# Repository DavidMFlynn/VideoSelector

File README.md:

# VideoSelector
Sets camera to monitor connections, RS-232, Extron Electronics MAV 88, PIC16F1847.
Created by David M. Flynn 2017
I could find one, so I built one.
The main pcb and selector switch pcbs are connected by ethernet patch cables.
Each station can select (with a gray code rotory encoder) which cammera to view.
Box 3D has a 3D printable box.

The PCBs are made with kicad.  Two of the wires on port 2 are swapped, fixed in software.
I know its unlikely anyone will want one, but it makes a good example project.

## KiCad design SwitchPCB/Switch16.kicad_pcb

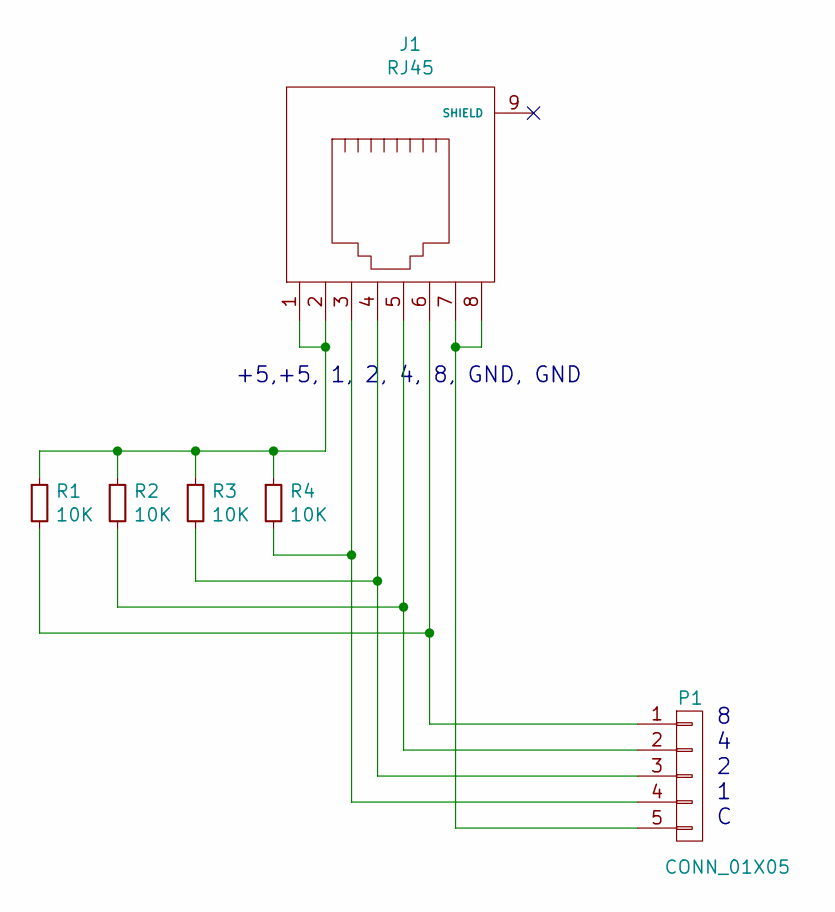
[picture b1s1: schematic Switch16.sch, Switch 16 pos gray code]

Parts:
J1: RJ45; RJ45_8
P1: CONN_01X05; Pin_Header_Straight_1x05
R1, R2, R3, R4: 10K; R_0805_HandSoldering

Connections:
unnamed: J1.1, J1.2, R1.1, R2.1, R3.1, R4.1
unnamed: J1.3, P1.4, R4.2
unnamed: J1.4, P1.3, R3.2
unnamed: J1.5, P1.2, R2.2
unnamed: J1.6, P1.1, R1.2
unnamed: J1.7, J1.8, P1.5

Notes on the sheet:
8 4 2 1 C
+5,+5, 1, 2, 4, 8, GND, GND

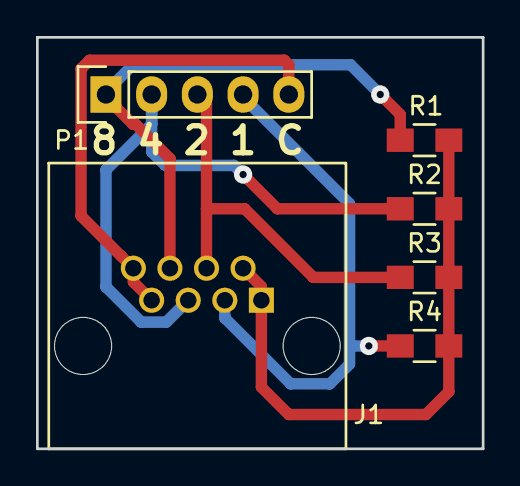
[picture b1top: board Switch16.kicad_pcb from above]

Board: 2 copper layers, 24.8 x 22.9 mm, 6 parts (0 on the bottom side), 6 nets.

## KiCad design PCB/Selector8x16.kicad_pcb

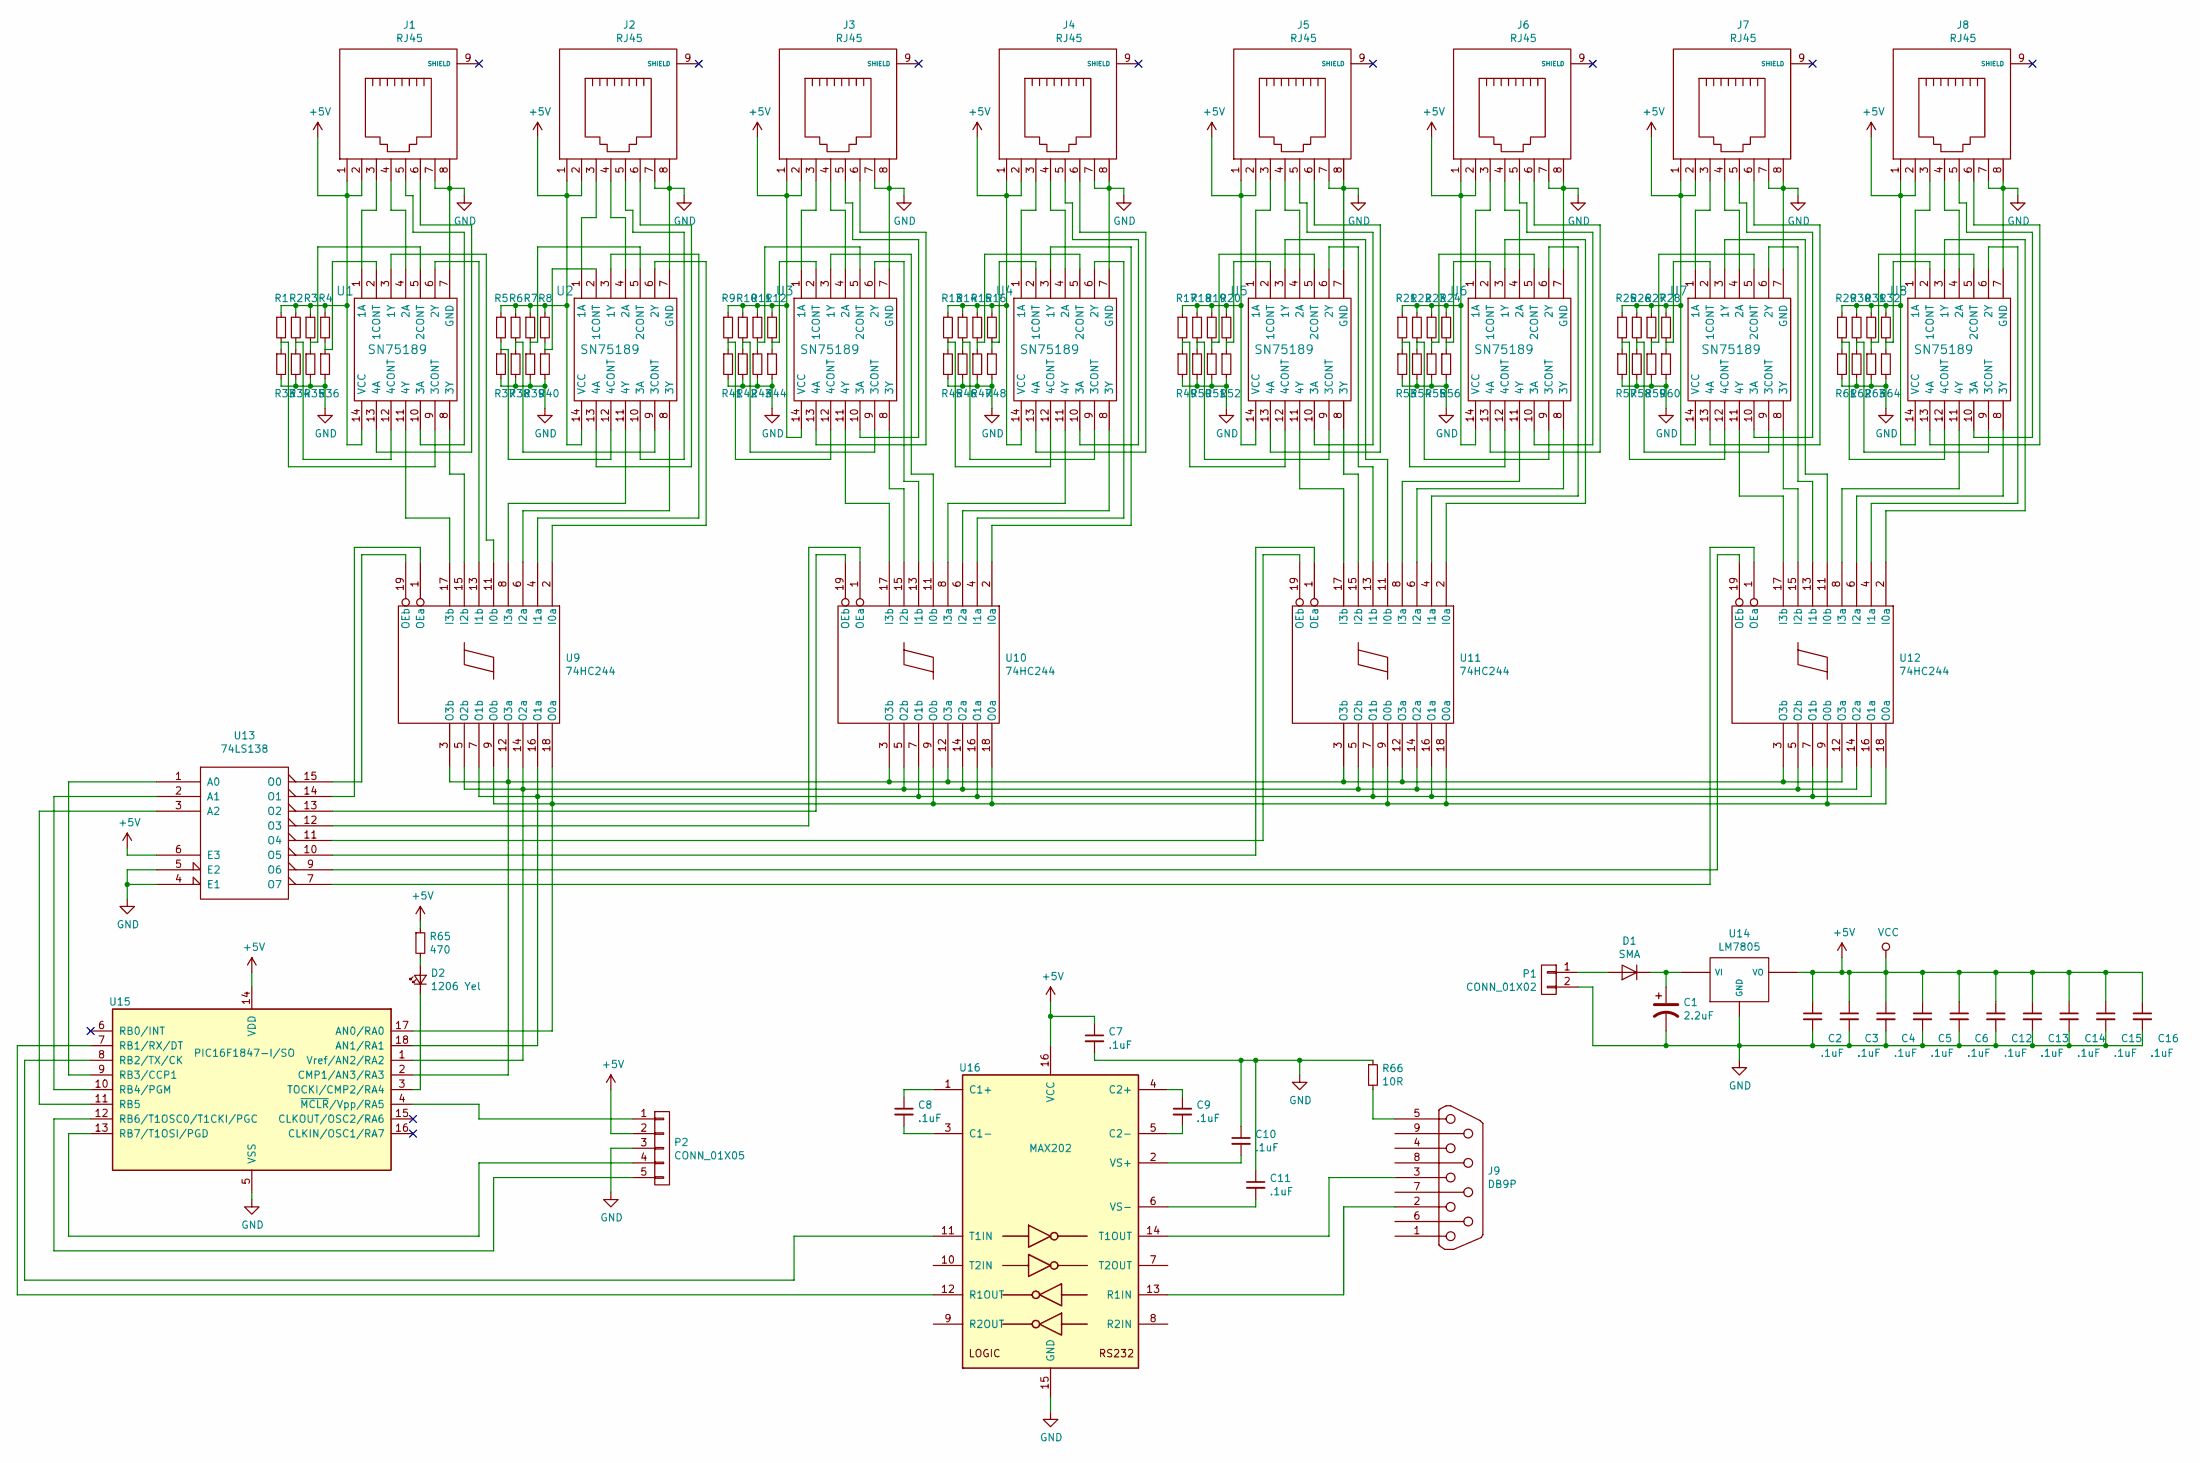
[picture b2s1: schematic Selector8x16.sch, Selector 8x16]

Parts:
C1: 2.2uF; C_Radial_D5_L11_P2
C2, C3, C4, C5, C6, C7, C8, C9, C10, C11, C12, C13, C14, C15, C16: .1uF; C_0805_HandSoldering
D1: SMA; SMA_Handsoldering
D2: 1206 Yel; LED_1206
J1, J2, J3, J4, J5, J6, J7, J8: RJ45
J9: DB9P; DB9MC
P1: CONN_01X02; bornier2
P2: CONN_01X05; Pin_Header_Straight_1x05
R1, R2, R3, R4, R5, R6, R7, R8, R9, R10, R11, R12, R13, R14, R15, R16, R17, R18, R19, R20, R21, R22, R23, R24, R25, R26, R27, R28, R29, R30, R31, R32, R33, R34, R35, R36, R37, R38, R39, R40, R41, R42, R43, R44, R45, R46, R47, R48, R49, R50, R51, R52, R53, R54, R55, R56, R57, R58, R59, R60, R61, R62, R63, R64: 10K; R_0805_HandSoldering
R65: 470; R_0805_HandSoldering
R66: 10R; R_0805_HandSoldering
U1, U2, U3, U4, U5, U6, U7, U8: SN75189; SOIC-14_3.9x8.7mm_Pitch1.27mm
U9, U10, U11, U12: 74HC244; SOIC-20W_7.5x12.8mm_Pitch1.27mm
U13: 74LS138; SOIC-16_3.9x9.9mm_Pitch1.27mm
U14: LM7805; TO-220_Neutral123_Horizontal
U15: PIC16F1847-I/SO; SOIC-18W_7.5x11.6mm_Pitch1.27mm
U16: MAX202; SOIC-16W_7.5x10.3mm_Pitch1.27mm

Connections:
+5V: C2.1, C3.1, C4.1, C5.1, C6.1, C7.1, C12.1, C13.1, C14.1, C15.1, C16.1, J1.1, J1.2, J2.1, J2.2, J3.1, J3.2, J4.1, J4.2, J5.1, J5.2, J6.1, J6.2, J7.1, J7.2, J8.1, J8.2, P2.2, R1.1, R2.1, R3.1, R4.1, R5.1, R6.1, R7.1, R8.1, R9.1, R10.1, R11.1, R12.1, R13.1, R14.1, R15.1, R16.1, R17.1, R18.1, R19.1, R20.1, R21.1, R22.1, R23.1, R24.1, R25.1, R26.1, R27.1, R28.1, R29.1, R30.1, R31.1, R32.1, R65.1, U1.14 (VCC), U2.14 (VCC), U3.14 (VCC), U4.14 (VCC), U5.14 (VCC), U6.14 (VCC), U7.14 (VCC), U8.14 (VCC), U9.20 (VCC), U10.20 (VCC), U11.20 (VCC), U12.20 (VCC), U13.6 (E3), U13.16 (VCC), U14.VO, U15.14 (VDD), U16.16 (VCC)
GND: C1.2, C2.2, C3.2, C4.2, C5.2, C6.2, C7.2, C10.1, C11.1, C12.2, C13.2, C14.2, C15.2, C16.2, J1.7, J1.8, J2.7, J2.8, J3.7, J3.8, J4.7, J4.8, J5.7, J5.8, J6.7, J6.8, J7.7, J7.8, J8.7, J8.8, P1.2, P2.3, R33.2, R34.2, R35.2, R36.2, R37.2, R38.2, R39.2, R40.2, R41.2, R42.2, R43.2, R44.2, R45.2, R46.2, R47.2, R48.2, R49.2, R50.2, R51.2, R52.2, R53.2, R54.2, R55.2, R56.2, R57.2, R58.2, R59.2, R60.2, R61.2, R62.2, R63.2, R64.2, R66.1, U1.7 (GND), U2.7 (GND), U3.7 (GND), U4.7 (GND), U5.7 (GND), U6.7 (GND), U7.7 (GND), U8.7 (GND), U9.10 (GND), U10.10 (GND), U11.10 (GND), U12.10 (GND), U13.4 (E1), U13.5 (E2), U13.8 (GND), U14.GND, U15.5 (VSS), U16.15 (GND)
unnamed: C1.1, D1.1 (K), U14.VI
unnamed: C8.1, U16.1 (C1+)
unnamed: C8.2, U16.3 (C1-)
unnamed: C9.1, U16.4 (C2+)
unnamed: C9.2, U16.5 (C2-)
unnamed: C10.2, U16.2 (VS+)
unnamed: C11.2, U16.6 (VS-)
unnamed: D1.2 (A), P1.1
unnamed: D2.1 (K), U15.3 (TOCKI/CMP2/RA4)
unnamed: D2.2 (A), R65.2
unnamed: J1.3, U1.1 (1A)
unnamed: J1.4, U1.4 (2A)
unnamed: J1.5, U1.10 (3A)
unnamed: J1.6, U1.13 (4A)
unnamed: J2.3, U2.1 (1A)
unnamed: J2.4, U2.4 (2A)
unnamed: J2.5, U2.10 (3A)
unnamed: J2.6, U2.13 (4A)
unnamed: J3.3, U3.1 (1A)
unnamed: J3.4, U3.4 (2A)
unnamed: J3.5, U3.10 (3A)
unnamed: J3.6, U3.13 (4A)
unnamed: J4.3, U4.1 (1A)
unnamed: J4.4, U4.4 (2A)
unnamed: J4.5, U4.10 (3A)
unnamed: J4.6, U4.13 (4A)
unnamed: J5.3, U5.1 (1A)
unnamed: J5.4, U5.4 (2A)
unnamed: J5.5, U5.10 (3A)
unnamed: J5.6, U5.13 (4A)
unnamed: J6.3, U6.1 (1A)
unnamed: J6.4, U6.4 (2A)
unnamed: J6.5, U6.10 (3A)
unnamed: J6.6, U6.13 (4A)
unnamed: J7.3, U7.1 (1A)
unnamed: J7.4, U7.4 (2A)
unnamed: J7.5, U7.10 (3A)
unnamed: J7.6, U7.13 (4A)
unnamed: J8.3, U8.1 (1A)
unnamed: J8.4, U8.4 (2A)
unnamed: J8.5, U8.10 (3A)
unnamed: J8.6, U8.13 (4A)
unnamed: J9.2, U16.13 (R1IN)
unnamed: J9.3, U16.14 (T1OUT)
unnamed: J9.5, R66.2
unnamed: P2.1, U15.4 (~MCLR~/Vpp/RA5)
unnamed: P2.4, U15.13 (RB7/T1OSI/PGD)
unnamed: P2.5, U15.12 (RB6/T1OSC0/T1CKI/PGC)
unnamed: R1.2, R33.1, U1.9 (3CONT)
unnamed: R2.2, R34.1, U1.12 (4CONT)
unnamed: R3.2, R35.1, U1.5 (2CONT)
unnamed: R10.2, R42.1, U3.9 (3CONT)
unnamed: R11.2, R43.1, U3.5 (2CONT)
unnamed: R12.2, R44.1, U3.2 (1CONT)
unnamed: R13.2, R45.1, U4.12 (4CONT)
unnamed: R14.2, R46.1, U4.9 (3CONT)
unnamed: R15.2, R47.1, U4.5 (2CONT)
unnamed: R16.2, R48.1, U4.2 (1CONT)
unnamed: R17.2, R49.1, U5.12 (4CONT)
unnamed: R18.2, R50.1, U5.9 (3CONT)
unnamed: R19.2, R51.1, U5.5 (2CONT)
unnamed: R20.2, R52.1, U5.2 (1CONT)
unnamed: R21.2, R53.1, U6.12 (4CONT)
unnamed: R22.2, R54.1, U6.9 (3CONT)
unnamed: R23.2, R55.1, U6.5 (2CONT)
unnamed: R24.2, R56.1, U6.2 (1CONT)
unnamed: R25.2, R57.1, U7.12 (4CONT)
unnamed: R26.2, R58.1, U7.9 (3CONT)
unnamed: R27.2, R59.1, U7.5 (2CONT)
unnamed: R28.2, R60.1, U7.2 (1CONT)
unnamed: R29.2, R61.1, U8.12 (4CONT)
unnamed: R30.2, R62.1, U8.9 (3CONT)
unnamed: R31.2, R63.1, U8.5 (2CONT)
unnamed: R32.2, R64.1, U8.2 (1CONT)
unnamed: R4.2, R36.1, U1.2 (1CONT)
unnamed: R5.2, R37.1, U2.12 (4CONT)
unnamed: R6.2, R38.1, U2.9 (3CONT)
unnamed: R7.2, R39.1, U2.5 (2CONT)
unnamed: R8.2, R40.1, U2.2 (1CONT)
unnamed: R9.2, R41.1, U3.12 (4CONT)
unnamed: U1.3 (1Y), U9.11 (I0b)
unnamed: U1.6 (2Y), U9.13 (I1b)
unnamed: U1.8 (3Y), U9.15 (I2b)
unnamed: U1.11 (4Y), U9.17 (I3b)
unnamed: U2.3 (1Y), U9.4 (I1a)
unnamed: U2.6 (2Y), U9.2 (I0a)
unnamed: U2.8 (3Y), U9.6 (I2a)
unnamed: U2.11 (4Y), U9.8 (I3a)
unnamed: U10.1 (OEa), U13.12 (O3)
unnamed: U4.3 (1Y), U10.2 (I0a)
unnamed: U4.6 (2Y), U10.4 (I1a)
unnamed: U4.8 (3Y), U10.6 (I2a)
unnamed: U4.11 (4Y), U10.8 (I3a)
unnamed: U3.3 (1Y), U10.11 (I0b)
unnamed: U9.3 (O3b), U9.12 (O3a), U10.3 (O3b), U10.12 (O3a), U11.3 (O3b), U11.12 (O3a), U12.3 (O3b), U12.12 (O3a), U15.2 (CMP1/AN3/RA3)
unnamed: U3.6 (2Y), U10.13 (I1b)
unnamed: U9.5 (O2b), U9.14 (O2a), U10.5 (O2b), U10.14 (O2a), U11.5 (O2b), U11.14 (O2a), U12.5 (O2b), U12.14 (O2a), U15.1 (Vref/AN2/RA2)
unnamed: U3.8 (3Y), U10.15 (I2b)
unnamed: U9.7 (O1b), U9.16 (O1a), U10.7 (O1b), U10.16 (O1a), U11.7 (O1b), U11.16 (O1a), U12.7 (O1b), U12.16 (O1a), U15.18 (AN1/RA1)
unnamed: U3.11 (4Y), U10.17 (I3b)
unnamed: U9.9 (O0b), U9.18 (O0a), U10.9 (O0b), U10.18 (O0a), U11.9 (O0b), U11.18 (O0a), U12.9 (O0b), U12.18 (O0a), U15.17 (AN0/RA0)
unnamed: U10.19 (OEb), U13.13 (O2)
unnamed: U11.1 (OEa), U13.10 (O5)
unnamed: U6.3 (1Y), U11.2 (I0a)
unnamed: U6.6 (2Y), U11.4 (I1a)
unnamed: U6.8 (3Y), U11.6 (I2a)
unnamed: U6.11 (4Y), U11.8 (I3a)
unnamed: U5.3 (1Y), U11.11 (I0b)
unnamed: U5.6 (2Y), U11.13 (I1b)
unnamed: U5.8 (3Y), U11.15 (I2b)
unnamed: U5.11 (4Y), U11.17 (I3b)
unnamed: U11.19 (OEb), U13.11 (O4)
unnamed: U12.1 (OEa), U13.7 (O7)
unnamed: U8.3 (1Y), U12.2 (I0a)
unnamed: U8.6 (2Y), U12.4 (I1a)
unnamed: U8.8 (3Y), U12.6 (I2a)
unnamed: U8.11 (4Y), U12.8 (I3a)
unnamed: U7.3 (1Y), U12.11 (I0b)
unnamed: U7.6 (2Y), U12.13 (I1b)
unnamed: U7.8 (3Y), U12.15 (I2b)
unnamed: U7.11 (4Y), U12.17 (I3b)
unnamed: U12.19 (OEb), U13.9 (O6)
unnamed: U13.1 (A0), U15.9 (RB3/CCP1)
unnamed: U13.2 (A1), U15.10 (RB4/PGM)
unnamed: U13.3 (A2), U15.11 (RB5)
unnamed: U9.1 (OEa), U13.14 (O1)
unnamed: U9.19 (OEb), U13.15 (O0)
unnamed: U15.7 (RB1/RX/DT), U16.12 (R1OUT)
unnamed: U15.8 (RB2/TX/CK), U16.11 (T1IN)

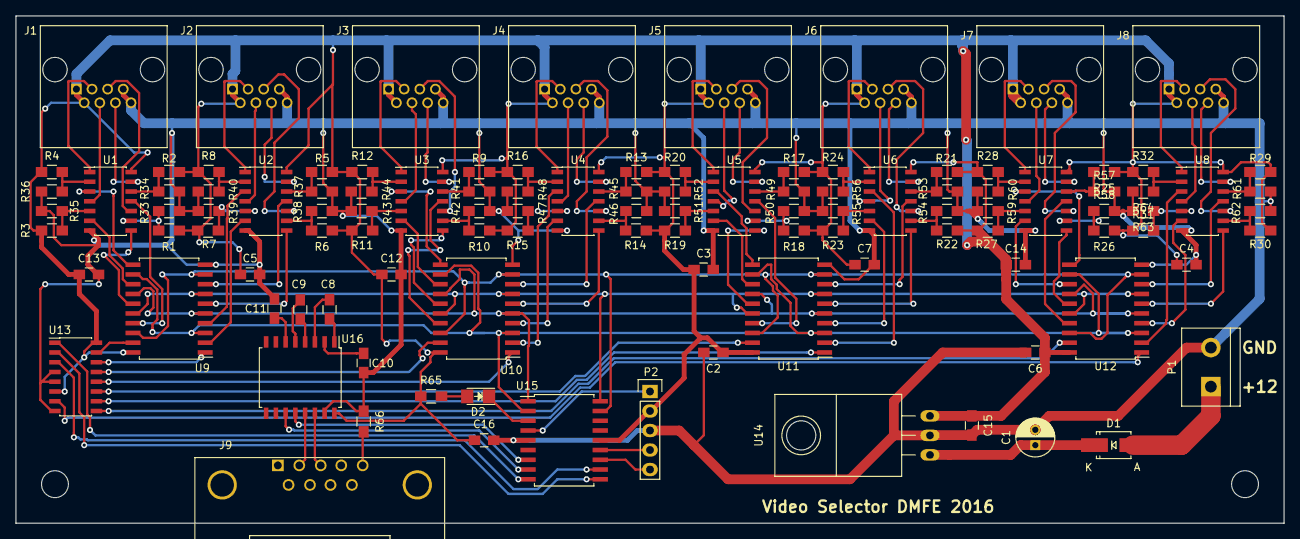
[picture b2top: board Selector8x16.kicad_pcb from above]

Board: 2 copper layers, 165.1 x 66.0 mm, 113 parts (0 on the bottom side), 131 nets.

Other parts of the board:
H1, H2: MountingHole_3.5mm

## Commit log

2017-03-02 Here it is...
    Done and working
2017-05-18 It didn't like the cr
